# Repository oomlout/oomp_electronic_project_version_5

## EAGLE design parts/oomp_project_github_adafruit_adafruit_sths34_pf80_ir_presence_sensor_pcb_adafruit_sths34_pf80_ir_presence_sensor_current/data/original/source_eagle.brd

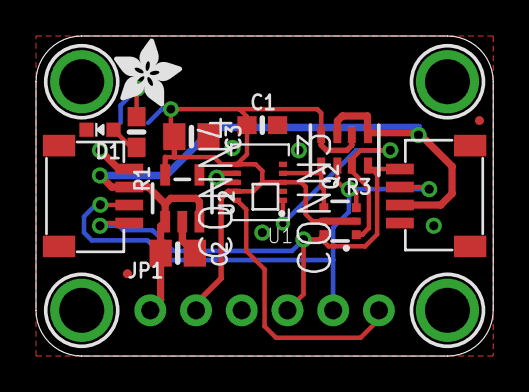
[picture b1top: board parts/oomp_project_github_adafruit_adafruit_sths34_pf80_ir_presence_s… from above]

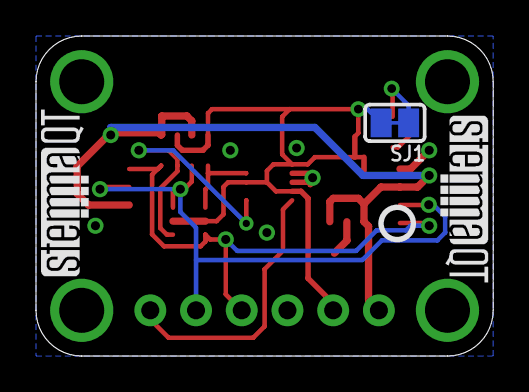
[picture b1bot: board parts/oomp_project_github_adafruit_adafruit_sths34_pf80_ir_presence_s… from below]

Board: 2 copper layers, 25.4 x 17.8 mm, 36 parts (8 on the bottom side), 10 nets.

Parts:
C1: 0.1uF; 0603-NO
C2, C3: 10uF; 0805-NO
CONN3, CONN4: STEMMA_I2C_QT; JST_SH4
D1: GREEN; CHIPLED_0603_NOOUTLINE
FID3, FID4: FIDUCIAL_0.5MM
JP1: 1X06_ROUND_70
PLABEL0: PLABEL0
PLABEL1: PLABEL1
PLABEL2: PLABEL2
PLABEL3: PLABEL3
PLABEL4: PLABEL4
PLABEL5: PLABEL5
PLABEL6: PLABEL6
PLABEL7: PLABEL7
PLABEL8: PLABEL8
PLABEL9: PLABEL9
PLABEL10: PLABEL10
PLABEL11: PLABEL11
PLABEL12: PLABEL12
Q2: BSS138; SOT363
R1: 10K; 0603-NO
R3: 10K Pack; RESPACK_4X0603
SJ1: SOLDERJUMPER_CLOSEDWIRE
U1: STHS34PF80TR; XDCR_STHS34PF80TR
U2: AP2127K-3.3; SOT23-5
U$1, U$17, U$19, U$21: MOUNTINGHOLE2.5; MOUNTINGHOLE_2.5_PLATED
U$22: ADAFRUIT_3.5MM
U$25: PCBFEAT-REV-040
U$30, U$31: STEMMAQT

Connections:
3.3V: C1.1, C3.1, JP1.2, Q2.2, Q2.5, R3.2, R3.4, SJ1.2, U1.3, U1.6, U1.9, U2.5
GND: C1.2, C2.2, C3.2, CONN3.1, CONN3.MT1, CONN3.MT2, CONN4.1, CONN4.MT1, CONN4.MT2, D1.C, JP1.3, U1.2, U1.7, U1.8, U2.2
INT: JP1.6, U1.10
unnamed: D1.A, R1.2
unnamed: R1.1, SJ1.1
SCL: CONN3.4, CONN4.4, JP1.4, Q2.6, R3.8
SCL_3V: Q2.1, R3.7, U1.1
SDA: CONN3.3, CONN4.3, JP1.5, Q2.3, R3.6
SDA_3V: Q2.4, R3.5, U1.4
VCC: C2.1, CONN3.2, CONN4.2, JP1.1, R3.1, R3.3, U2.1, U2.3

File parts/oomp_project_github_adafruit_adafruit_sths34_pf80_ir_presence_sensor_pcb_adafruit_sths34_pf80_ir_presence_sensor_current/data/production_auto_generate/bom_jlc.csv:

Comment,Designator,Footprint,LCSC Part #
,JP1,Adafruit STHS34PF80 IR Presence Sensor-import-fps:1X06_ROUND_70,C37208
,U$22,Adafruit STHS34PF80 IR Presence Sensor-import-fps:ADAFRUIT_3.5MM,
,U$25,Adafruit STHS34PF80 IR Presence Sensor-import-fps:PCBFEAT-REV-040,
,PLABEL0,Adafruit STHS34PF80 IR Presence Sensor-import-fps:PLABEL0,
,PLABEL1,Adafruit STHS34PF80 IR Presence Sensor-import-fps:PLABEL1,
,PLABEL10,Adafruit STHS34PF80 IR Presence Sensor-import-fps:PLABEL10,
,PLABEL11,Adafruit STHS34PF80 IR Presence Sensor-import-fps:PLABEL11,
,PLABEL12,Adafruit STHS34PF80 IR Presence Sensor-import-fps:PLABEL12,
,PLABEL2,Adafruit STHS34PF80 IR Presence Sensor-import-fps:PLABEL2,
,PLABEL3,Adafruit STHS34PF80 IR Presence Sensor-import-fps:PLABEL3,
,PLABEL4,Adafruit STHS34PF80 IR Presence Sensor-import-fps:PLABEL4,
,PLABEL5,Adafruit STHS34PF80 IR Presence Sensor-import-fps:PLABEL5,
,PLABEL6,Adafruit STHS34PF80 IR Presence Sensor-import-fps:PLABEL6,
,PLABEL7,Adafruit STHS34PF80 IR Presence Sensor-import-fps:PLABEL7,
,PLABEL8,Adafruit STHS34PF80 IR Presence Sensor-import-fps:PLABEL8,
,PLABEL9,Adafruit STHS34PF80 IR Presence Sensor-import-fps:PLABEL9,
,"U$30,U$31",Adafruit STHS34PF80 IR Presence Sensor-import-fps:STEMMAQT,
0.1uF,C1,Adafruit STHS34PF80 IR Presence Sensor-import-fps:0603-NO,C14663
10K,R1,Adafruit STHS34PF80 IR Presence Sensor-import-fps:0603-NO,C98220
10K Pack,R3,Adafruit STHS34PF80 IR Presence Sensor-import-fps:RESPACK_4X0603,C98220
10uF,"C2,C3",Adafruit STHS34PF80 IR Presence Sensor-import-fps:0805-NO,
AP2127K-3.3,U2,Adafruit STHS34PF80 IR Presence Sensor-import-fps:SOT23-5,
BSS138,Q2,Adafruit STHS34PF80 IR Presence Sensor-import-fps:SOT363,
GREEN,D1,Adafruit STHS34PF80 IR Presence Sensor-import-fps:CHIPLED_0603_NOOUTLINE,
STEMMA_I2C_QT,"CONN3,CONN4",Adafruit STHS34PF80 IR Presence Sensor-import-fps:JST_SH4,C160404
STHS34PF80TR,U1,Adafruit STHS34PF80 IR Presence Sensor-import-fps:XDCR_STHS34PF80TR,

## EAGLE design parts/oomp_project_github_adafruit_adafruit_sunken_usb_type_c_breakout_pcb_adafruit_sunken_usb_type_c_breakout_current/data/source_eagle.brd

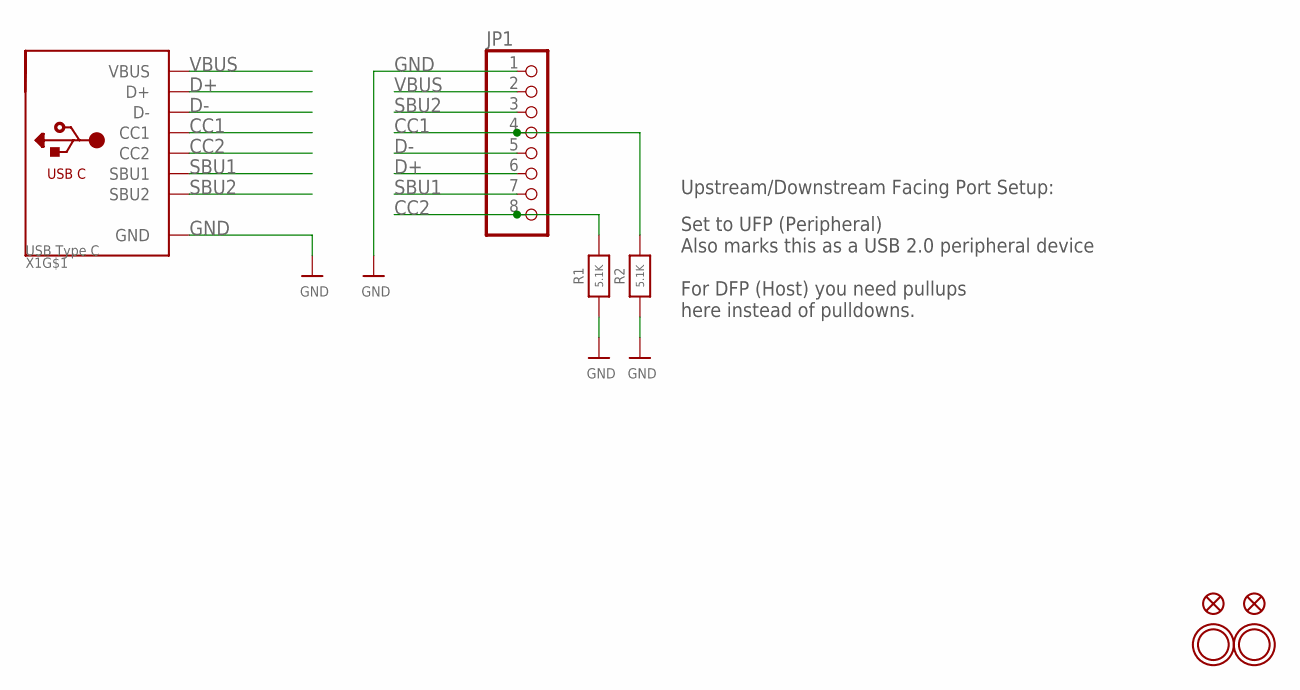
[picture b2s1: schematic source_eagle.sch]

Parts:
FID1, FID2: FIDUCIAL_0.5MM
JP1: HEADER-1X876MIL; 1X08_ROUND_76
R1, R2: 5.1K; 0603-NO
U$1, U$2: MOUNTINGHOLE2.5; MOUNTINGHOLE_2.5_PLATED
X1: USB Type C; USB_C_SINK

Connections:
CC1: JP1.4, R2.2, X1.A5 (CC1)
CC2: JP1.8, R1.2, X1.B5 (CC2)
D+: JP1.6, X1.A6 (D+), X1.B6 (D+)
D-: JP1.5, X1.A7 (D-), X1.B7 (D-)
GND: JP1.1, R1.1, R2.1, X1.A1B12 (GND), X1.B1A12 (GND)
SBU1: JP1.7, X1.A8 (SBU1)
SBU2: JP1.3, X1.B8 (SBU2)
VBUS: JP1.2, X1.A4B9 (VBUS), X1.B4A9 (VBUS)

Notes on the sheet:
Set to UFP (Peripheral) Also marks this as a USB 2.0 peripheral device For DFP (Host) you need pullups here instead of pulldowns.
Upstream/Downstream Facing Port Setup:

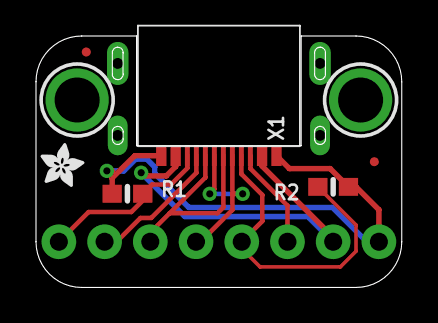
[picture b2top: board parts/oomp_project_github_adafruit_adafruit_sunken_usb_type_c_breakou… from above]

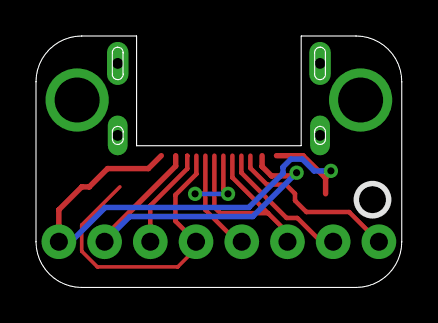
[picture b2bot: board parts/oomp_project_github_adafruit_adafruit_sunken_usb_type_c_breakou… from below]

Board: 2 copper layers, 20.3 x 14.0 mm, 21 parts (3 on the bottom side), 8 nets.

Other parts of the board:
PLABEL0: PLABEL0
PLABEL1: PLABEL1
PLABEL2: PLABEL2
PLABEL3: PLABEL3
PLABEL4: PLABEL4
PLABEL5: PLABEL5
PLABEL6: PLABEL6
PLABEL7: PLABEL7
PLABEL8: PLABEL8
PLABEL9: PLABEL9
PLABEL10: PLABEL10
U$3: ADAFRUIT_2.5MM
U$8: PCBFEAT-REV-040

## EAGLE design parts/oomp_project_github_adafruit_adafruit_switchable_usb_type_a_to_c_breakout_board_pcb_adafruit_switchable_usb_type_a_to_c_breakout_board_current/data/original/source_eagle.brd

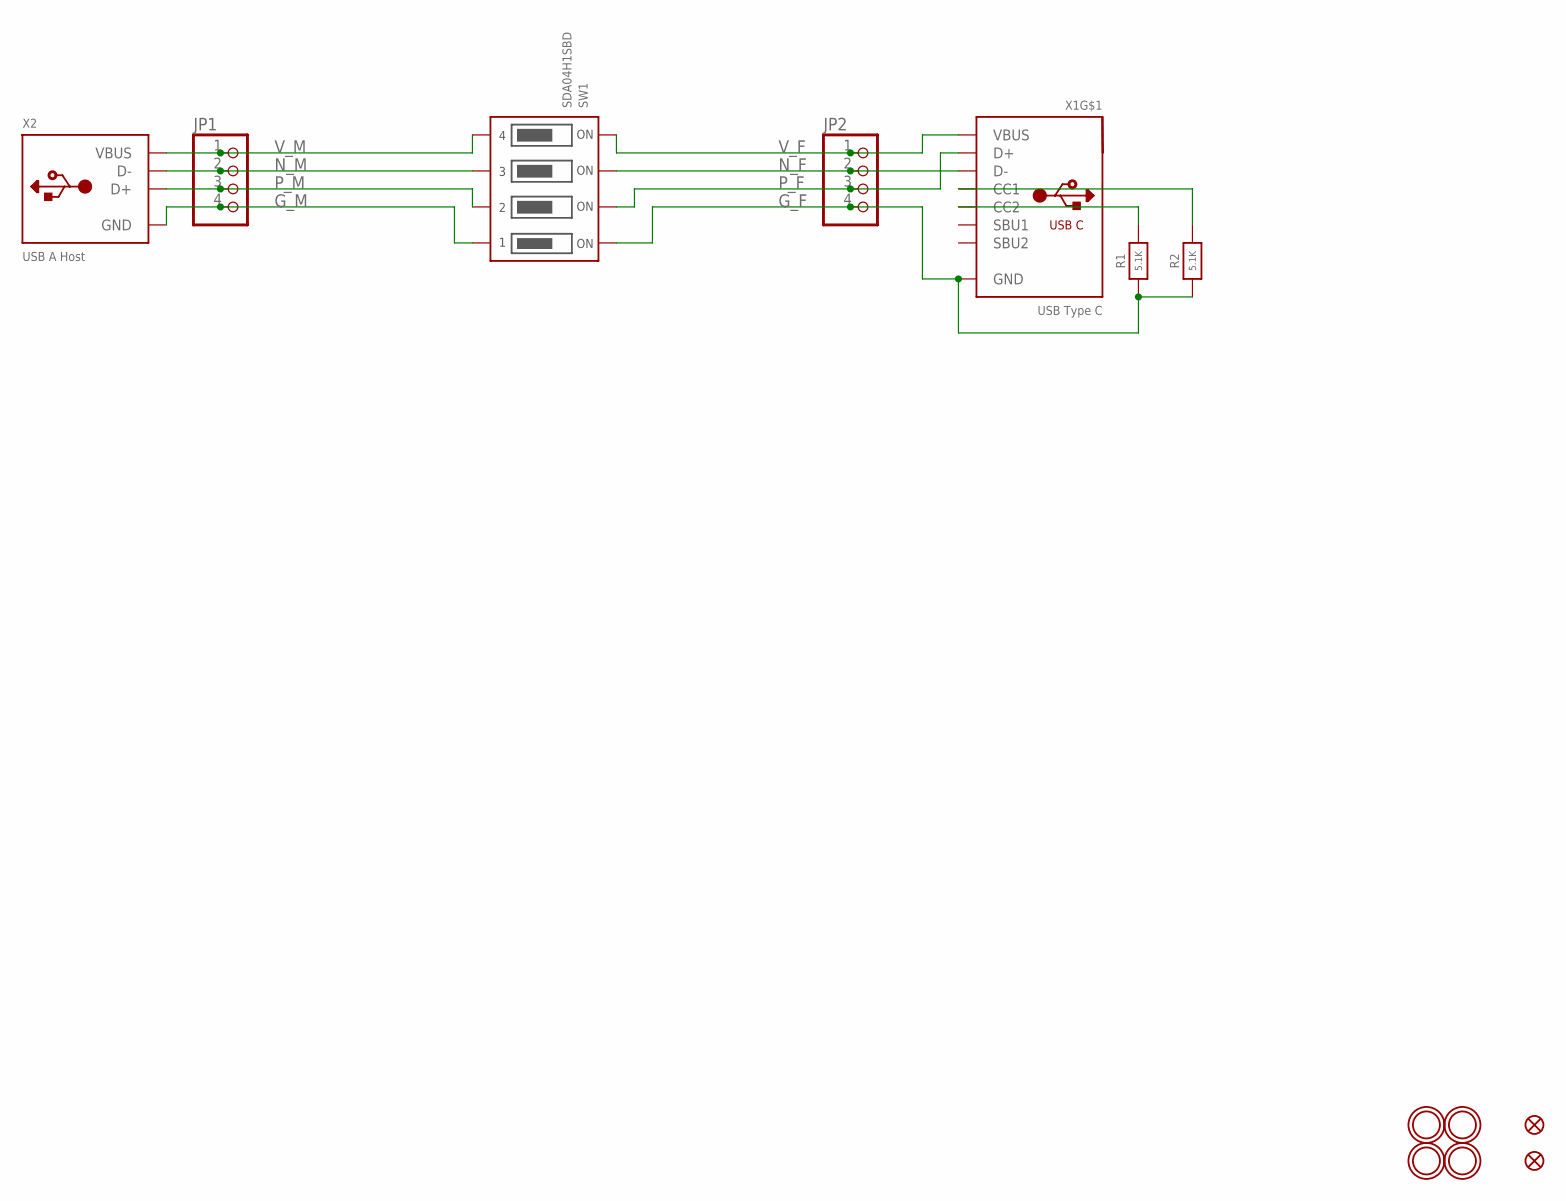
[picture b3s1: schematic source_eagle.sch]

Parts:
FID1, FID2: FIDUCIAL_1MM
JP1, JP2: HEADER-1X4ROUND; 1X04_ROUND
R1, R2: 5.1K; 0603-NO
SW1: SDA04H1SBD; DIPSWITCH_4PIN
U$1, U$2, U$3, U$4: MOUNTINGHOLE2.5; MOUNTINGHOLE_2.5_PLATED
X1: USB Type C; USB_C_CUSB31-CFM2AX-01-X
X2: USB A Host; USB_HOST-PTH

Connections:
G_F: JP2.4, R1.1, R2.1, SW1.1ON, X1.A1B12 (GND), X1.B1A12 (GND)
G_M: JP1.4, SW1.1OFF, X2.GND
unnamed: R1.2, X1.B5 (CC2)
unnamed: R2.2, X1.A5 (CC1)
N_F: JP2.2, SW1.3ON, X1.A7 (D-), X1.B7 (D-)
N_M: JP1.2, SW1.3OFF, X2.D-
P_F: JP2.3, SW1.2ON, X1.A6 (D+), X1.B6 (D+)
P_M: JP1.3, SW1.2OFF, X2.D+
V_F: JP2.1, SW1.4ON, X1.A4B9 (VBUS), X1.B4A9 (VBUS)
V_M: JP1.1, SW1.4OFF, X2.VBUS

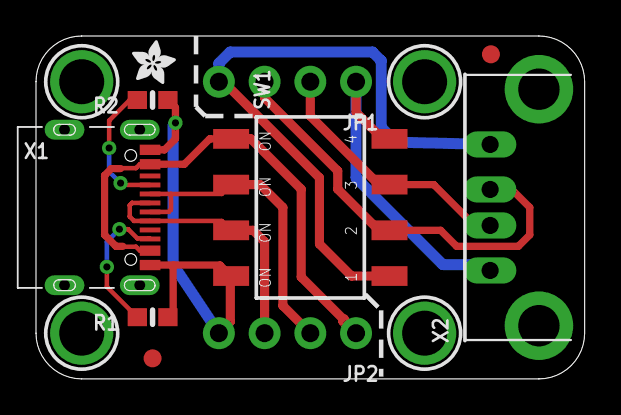
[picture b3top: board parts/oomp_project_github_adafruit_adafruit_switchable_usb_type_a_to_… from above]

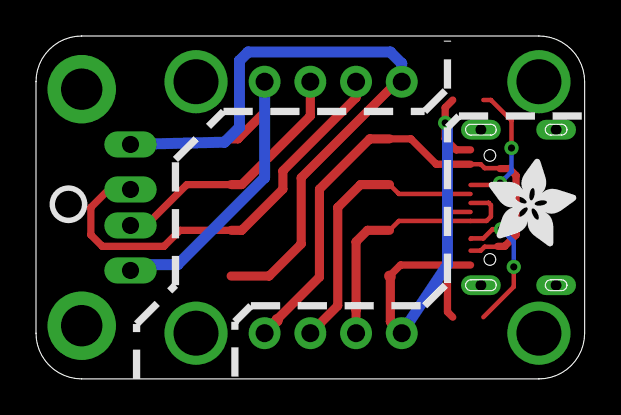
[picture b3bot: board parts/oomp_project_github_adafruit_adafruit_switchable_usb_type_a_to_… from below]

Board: 2 copper layers, 30.5 x 19.1 mm, 41 parts (11 on the bottom side), 10 nets.

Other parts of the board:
PLABEL0: PLABEL0
PLABEL1: PLABEL1
PLABEL2: PLABEL2
PLABEL3: PLABEL3
PLABEL4: PLABEL4
PLABEL5: PLABEL5
PLABEL6: PLABEL6
PLABEL7: PLABEL7
PLABEL8: PLABEL8
PLABEL9: PLABEL9
PLABEL10: PLABEL10
PLABEL11: PLABEL11
PLABEL12: PLABEL12
PLABEL13: PLABEL13
PLABEL14: PLABEL14
PLABEL15: PLABEL15
PLABEL16: PLABEL16
PLABEL17: PLABEL17
PLABEL18: PLABEL18
PLABEL19: PLABEL19
PLABEL20: PLABEL20
PLABEL21: PLABEL21
PLABEL22: PLABEL22
PLABEL23: PLABEL23
PLABEL24: PLABEL24
U$5: ADAFRUIT_2.5MM
U$6: ADAFRUIT_5MM
U$8: PCBFEAT-REV-040

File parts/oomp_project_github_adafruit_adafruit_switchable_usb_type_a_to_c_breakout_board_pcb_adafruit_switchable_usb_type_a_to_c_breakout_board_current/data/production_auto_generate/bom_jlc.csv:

Comment,Designator,Footprint,LCSC Part #
,"JP1,JP2",1X04_ROUND,C42431795
,U$5,ADAFRUIT_2.5MM,
,U$6,ADAFRUIT_5MM,
,U$8,PCBFEAT-REV-040,
,PLABEL0,PLABEL0,
,PLABEL1,PLABEL1,
,PLABEL10,PLABEL10,
,PLABEL11,PLABEL11,
,PLABEL12,PLABEL12,
,PLABEL13,PLABEL13,
,PLABEL14,PLABEL14,
,PLABEL15,PLABEL15,
,PLABEL16,PLABEL16,
,PLABEL17,PLABEL17,
,PLABEL18,PLABEL18,
,PLABEL19,PLABEL19,
,PLABEL2,PLABEL2,
,PLABEL20,PLABEL20,
,PLABEL21,PLABEL21,
,PLABEL22,PLABEL22,
,PLABEL23,PLABEL23,
,PLABEL24,PLABEL24,
,PLABEL3,PLABEL3,
,PLABEL4,PLABEL4,
,PLABEL5,PLABEL5,
,PLABEL6,PLABEL6,
,PLABEL7,PLABEL7,
,PLABEL8,PLABEL8,
,PLABEL9,PLABEL9,
5.1K,"R1,R2",0603-NO,C23186
SDA04H1SBD,SW1,DIPSWITCH_4PIN,
USB A Host,X2,USB_HOST-PTH,
USB Type C,X1,USB_C_CUSB31-CFM2AX-01-X,

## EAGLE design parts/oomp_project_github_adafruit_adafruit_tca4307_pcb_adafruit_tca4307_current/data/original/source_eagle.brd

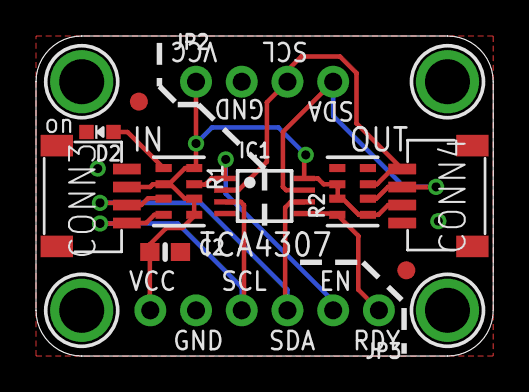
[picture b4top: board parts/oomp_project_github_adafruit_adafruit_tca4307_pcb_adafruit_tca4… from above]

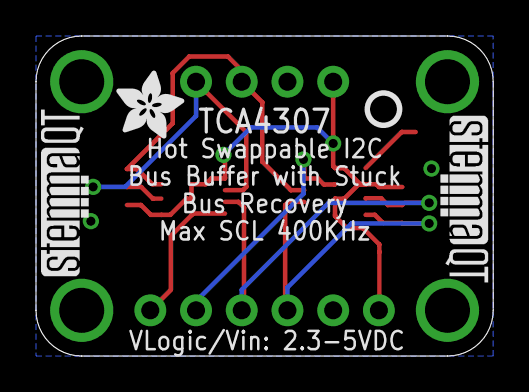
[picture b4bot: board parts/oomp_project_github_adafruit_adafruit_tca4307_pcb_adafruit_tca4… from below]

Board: 2 copper layers, 25.4 x 17.8 mm, 19 parts (4 on the bottom side), 9 nets.

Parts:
C2: 0.1uF; 0603-NO
CONN3, CONN4: STEMMA_I2C_QT; JST_SH4
D2: GREEN; CHIPLED_0603_NOOUTLINE
FID3, FID4: FIDUCIAL_1MM
IC1: TCA4307; TSSOP8
JP2: 1X04_ROUND
JP3: 1X06_ROUND_70
R1, R2: 10K; RESPACK_4X0603
U$1, U$17, U$19, U$21: MOUNTINGHOLE2.5; MOUNTINGHOLE_2.5_PLATED
U$2: ADAFRUIT_3.5MM
U$25: PCBFEAT-REV-040
U$30, U$31: STEMMAQT

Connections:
EN: IC1.1, JP3.2, R1.7
GND: C2.2, CONN3.1, CONN4.1, D2.C, IC1.4, JP2.2, JP3.5
unnamed: D2.A, R1.1
READY: IC1.5, JP3.1, R2.8
SCL_IN: CONN3.4, IC1.3, JP3.4, R1.4
SCL_OUT: CONN4.4, IC1.2, JP2.3, R2.3
SDA_IN: CONN3.3, IC1.6, JP3.3, R1.3
SDA_OUT: CONN4.3, IC1.7, JP2.4, R2.2
VCC: C2.1, CONN3.2, CONN4.2, IC1.8, JP2.1, JP3.6, R1.2, R1.5, R1.6, R1.8, R2.1, R2.6, R2.7

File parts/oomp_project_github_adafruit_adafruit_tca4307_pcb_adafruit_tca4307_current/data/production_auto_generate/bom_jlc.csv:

Comment,Designator,Footprint,LCSC Part #
,JP2,Adafruit TCA4307-import-fps:1X04_ROUND,C42431795
,JP3,Adafruit TCA4307-import-fps:1X06_ROUND_70,C37208
,U$2,Adafruit TCA4307-import-fps:ADAFRUIT_3.5MM,
,U$25,Adafruit TCA4307-import-fps:PCBFEAT-REV-040,
,"U$30,U$31",Adafruit TCA4307-import-fps:STEMMAQT,
0.1uF,C2,Adafruit TCA4307-import-fps:0603-NO,C14663
10K,"R1,R2",Adafruit TCA4307-import-fps:RESPACK_4X0603,C98220
GREEN,D2,Adafruit TCA4307-import-fps:CHIPLED_0603_NOOUTLINE,
STEMMA_I2C_QT,"CONN3,CONN4",Adafruit TCA4307-import-fps:JST_SH4,C160404
TCA4307,IC1,Adafruit TCA4307-import-fps:TSSOP8,

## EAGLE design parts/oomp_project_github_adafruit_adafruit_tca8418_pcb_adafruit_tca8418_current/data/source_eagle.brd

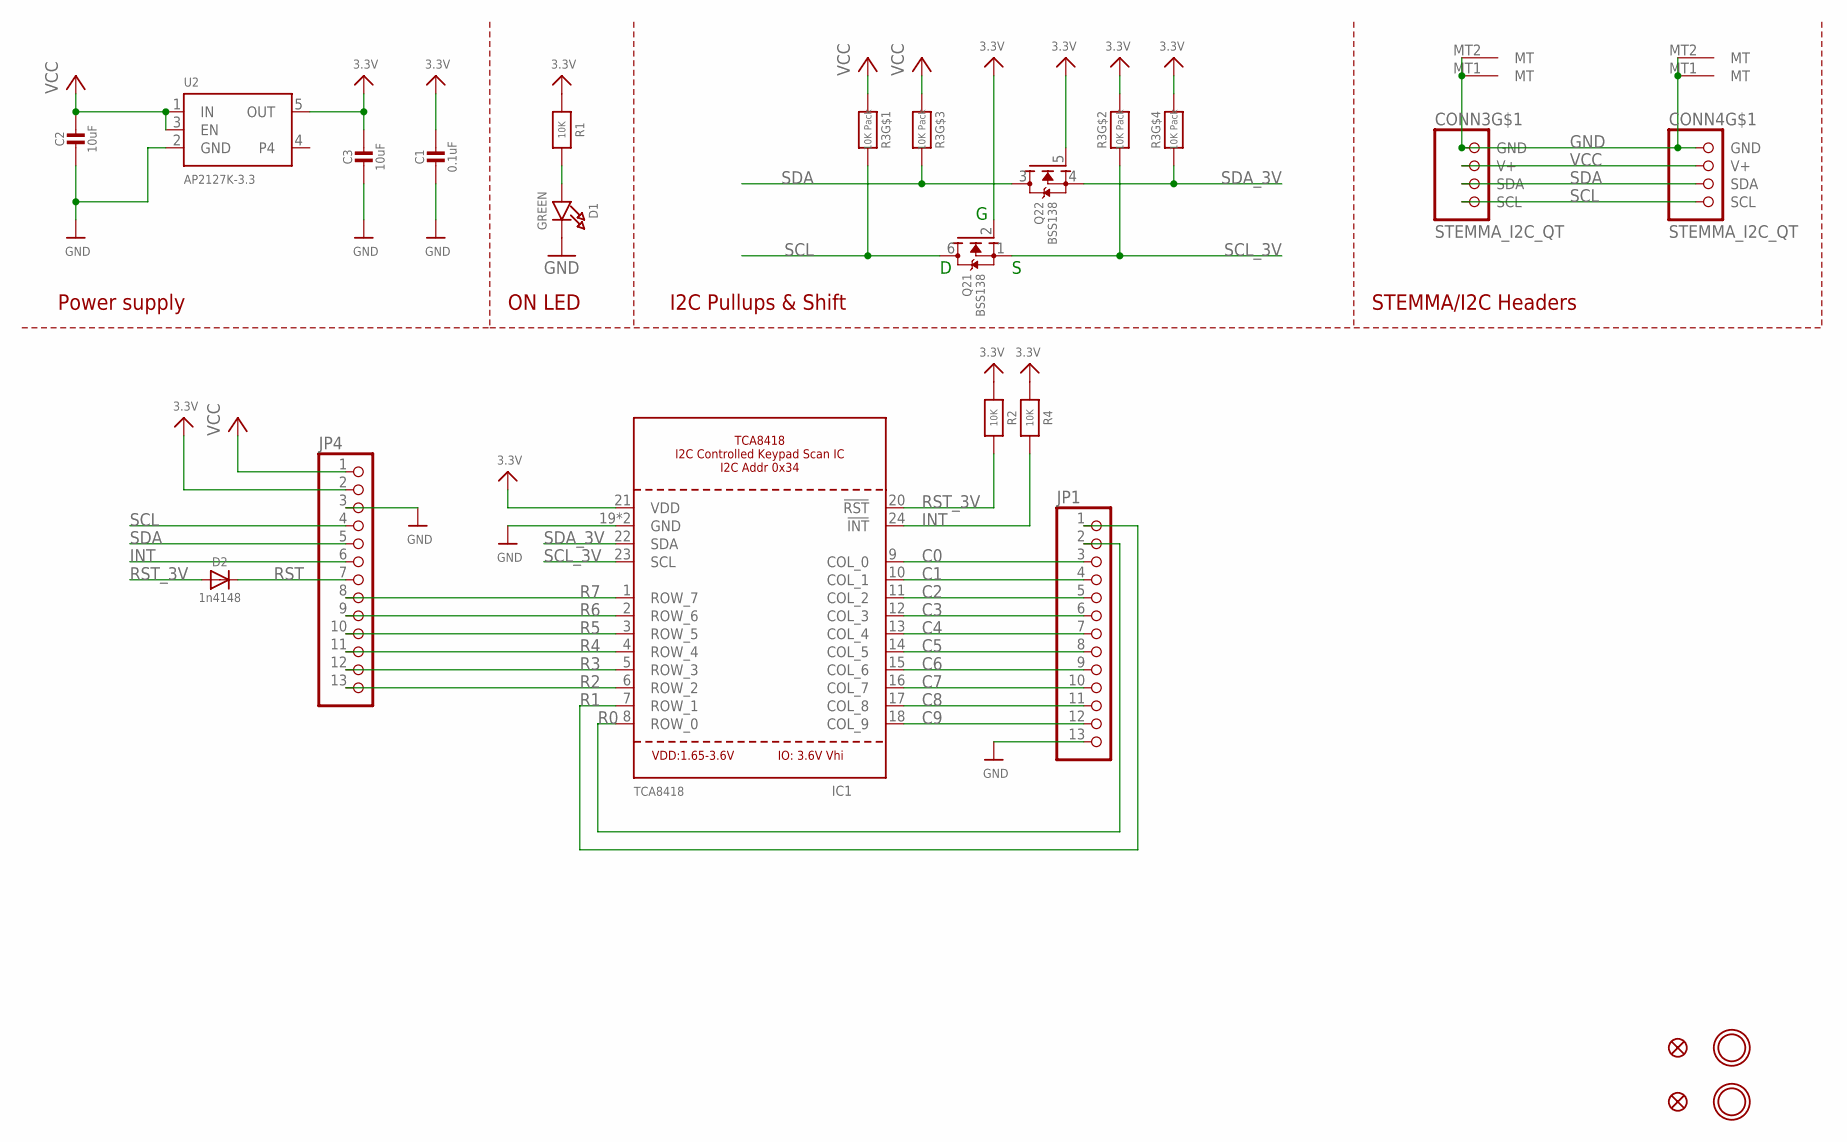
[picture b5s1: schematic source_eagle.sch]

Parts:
C1: 0.1uF; 0603-NO
C2, C3: 10uF; 0805-NO
CONN3, CONN4: STEMMA_I2C_QT; JST_SH4
D1: GREEN; CHIPLED_0603_NOOUTLINE
D2: 1n4148; SOD-323
FID3, FID4: FIDUCIAL_1MM
IC1: TCA8418; QFN24_4MM_SMSC
JP1, JP4: HEADER-1X13; 1X13_ROUND_70
Q2: BSS138; SOT363
R1, R2, R4: 10K; 0603-NO
R3: 10K Pack; RESPACK_4X0603
U2: AP2127K-3.3; SOT23-5
U$1, U$17: MOUNTINGHOLE2.5; MOUNTINGHOLE_2.5_PLATED

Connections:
3.3V: C1.1, C3.1, IC1.21 (VDD), JP4.2, Q2.2 (G), Q2.5 (G), R1.1, R2.1, R3.2 (1), R3.4 (1), R4.1, U2.5 (OUT)
C0: IC1.9 (COL_0), JP1.3
C1: IC1.10 (COL_1), JP1.4
C2: IC1.11 (COL_2), JP1.5
C3: IC1.12 (COL_3), JP1.6
C4: IC1.13 (COL_4), JP1.7
C5: IC1.14 (COL_5), JP1.8
C6: IC1.15 (COL_6), JP1.9
C7: IC1.16 (COL_7), JP1.10
C8: IC1.17 (COL_8), JP1.11
C9: IC1.18 (COL_9), JP1.12
GND: C1.2, C2.2, C3.2, CONN3.1 (GND), CONN3.MT1 (MT), CONN3.MT2 (MT), CONN4.1 (GND), CONN4.MT1 (MT), CONN4.MT2 (MT), D1.C, IC1.19 (GND), IC1.THERM (GND), JP1.13, JP4.3, U2.2 (GND)
INT: IC1.24 (!INT), JP4.6, R4.2
unnamed: D1.A, R1.2
R0: IC1.8 (ROW_0), JP1.2
R1: IC1.7 (ROW_1), JP1.1
R2: IC1.6 (ROW_2), JP4.13
R3: IC1.5 (ROW_3), JP4.12
R4: IC1.4 (ROW_4), JP4.11
R5: IC1.3 (ROW_5), JP4.10
R6: IC1.2 (ROW_6), JP4.9
R7: IC1.1 (ROW_7), JP4.8
RST: D2.C, JP4.7
RST_3V: D2.A, IC1.20 (!RST), R2.2
SCL: CONN3.4 (SCL), CONN4.4 (SCL), JP4.4, Q2.6 (D), R3.8 (2)
SCL_3V: IC1.23 (SCL), Q2.1 (S), R3.7 (2)
SDA: CONN3.3 (SDA), CONN4.3 (SDA), JP4.5, Q2.3 (D), R3.6 (2)
SDA_3V: IC1.22 (SDA), Q2.4 (S), R3.5 (2)
VCC: C2.1, CONN3.2 (V+), CONN4.2 (V+), JP4.1, R3.1, R3.3 (1), U2.1 (IN), U2.3 (EN)

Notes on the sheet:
I2C Pullups & Shift
STEMMA/I2C Headers
ON LED
Power supply

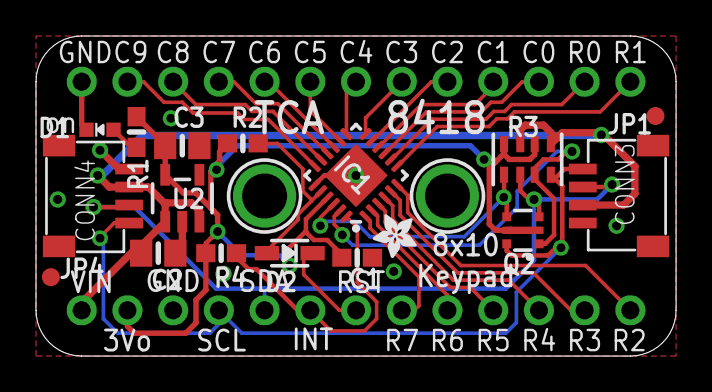
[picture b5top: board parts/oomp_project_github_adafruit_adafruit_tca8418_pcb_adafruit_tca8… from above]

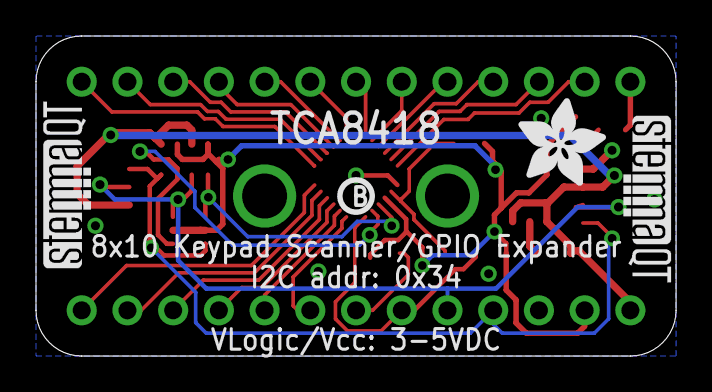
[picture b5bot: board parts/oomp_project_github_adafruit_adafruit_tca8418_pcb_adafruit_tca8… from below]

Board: 2 copper layers, 35.6 x 17.8 mm, 25 parts (4 on the bottom side), 29 nets.

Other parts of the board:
U$12: PCBFEAT-REV-040
U$19: ADAFRUIT_5MM
U$20: ADAFRUIT_2.5MM
U$30, U$31: STEMMAQT

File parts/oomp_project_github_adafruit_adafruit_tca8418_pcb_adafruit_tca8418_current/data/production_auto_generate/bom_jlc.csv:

Comment,Designator,Footprint,LCSC Part #
,"JP1,JP4",Adafruit TCA8418-import-fps:1X13_ROUND_70,C2894936
,U$20,Adafruit TCA8418-import-fps:ADAFRUIT_2.5MM,
,U$19,Adafruit TCA8418-import-fps:ADAFRUIT_5MM,
,U$12,Adafruit TCA8418-import-fps:PCBFEAT-REV-040,
,"U$30,U$31",Adafruit TCA8418-import-fps:STEMMAQT,
0.1uF,C1,Adafruit TCA8418-import-fps:0603-NO,C14663
10K,"R1,R2,R4",Adafruit TCA8418-import-fps:0603-NO,C98220
10K Pack,R3,Adafruit TCA8418-import-fps:RESPACK_4X0603,C98220
10uF,"C2,C3",Adafruit TCA8418-import-fps:0805-NO,
1n4148,D2,Adafruit TCA8418-import-fps:SOD-323,
AP2127K-3.3,U2,Adafruit TCA8418-import-fps:SOT23-5,
BSS138,Q2,Adafruit TCA8418-import-fps:SOT363,
GREEN,D1,Adafruit TCA8418-import-fps:CHIPLED_0603_NOOUTLINE,
STEMMA_I2C_QT,"CONN3,CONN4",Adafruit TCA8418-import-fps:JST_SH4,C160404
TCA8418,IC1,Adafruit TCA8418-import-fps:QFN24_4MM_SMSC,

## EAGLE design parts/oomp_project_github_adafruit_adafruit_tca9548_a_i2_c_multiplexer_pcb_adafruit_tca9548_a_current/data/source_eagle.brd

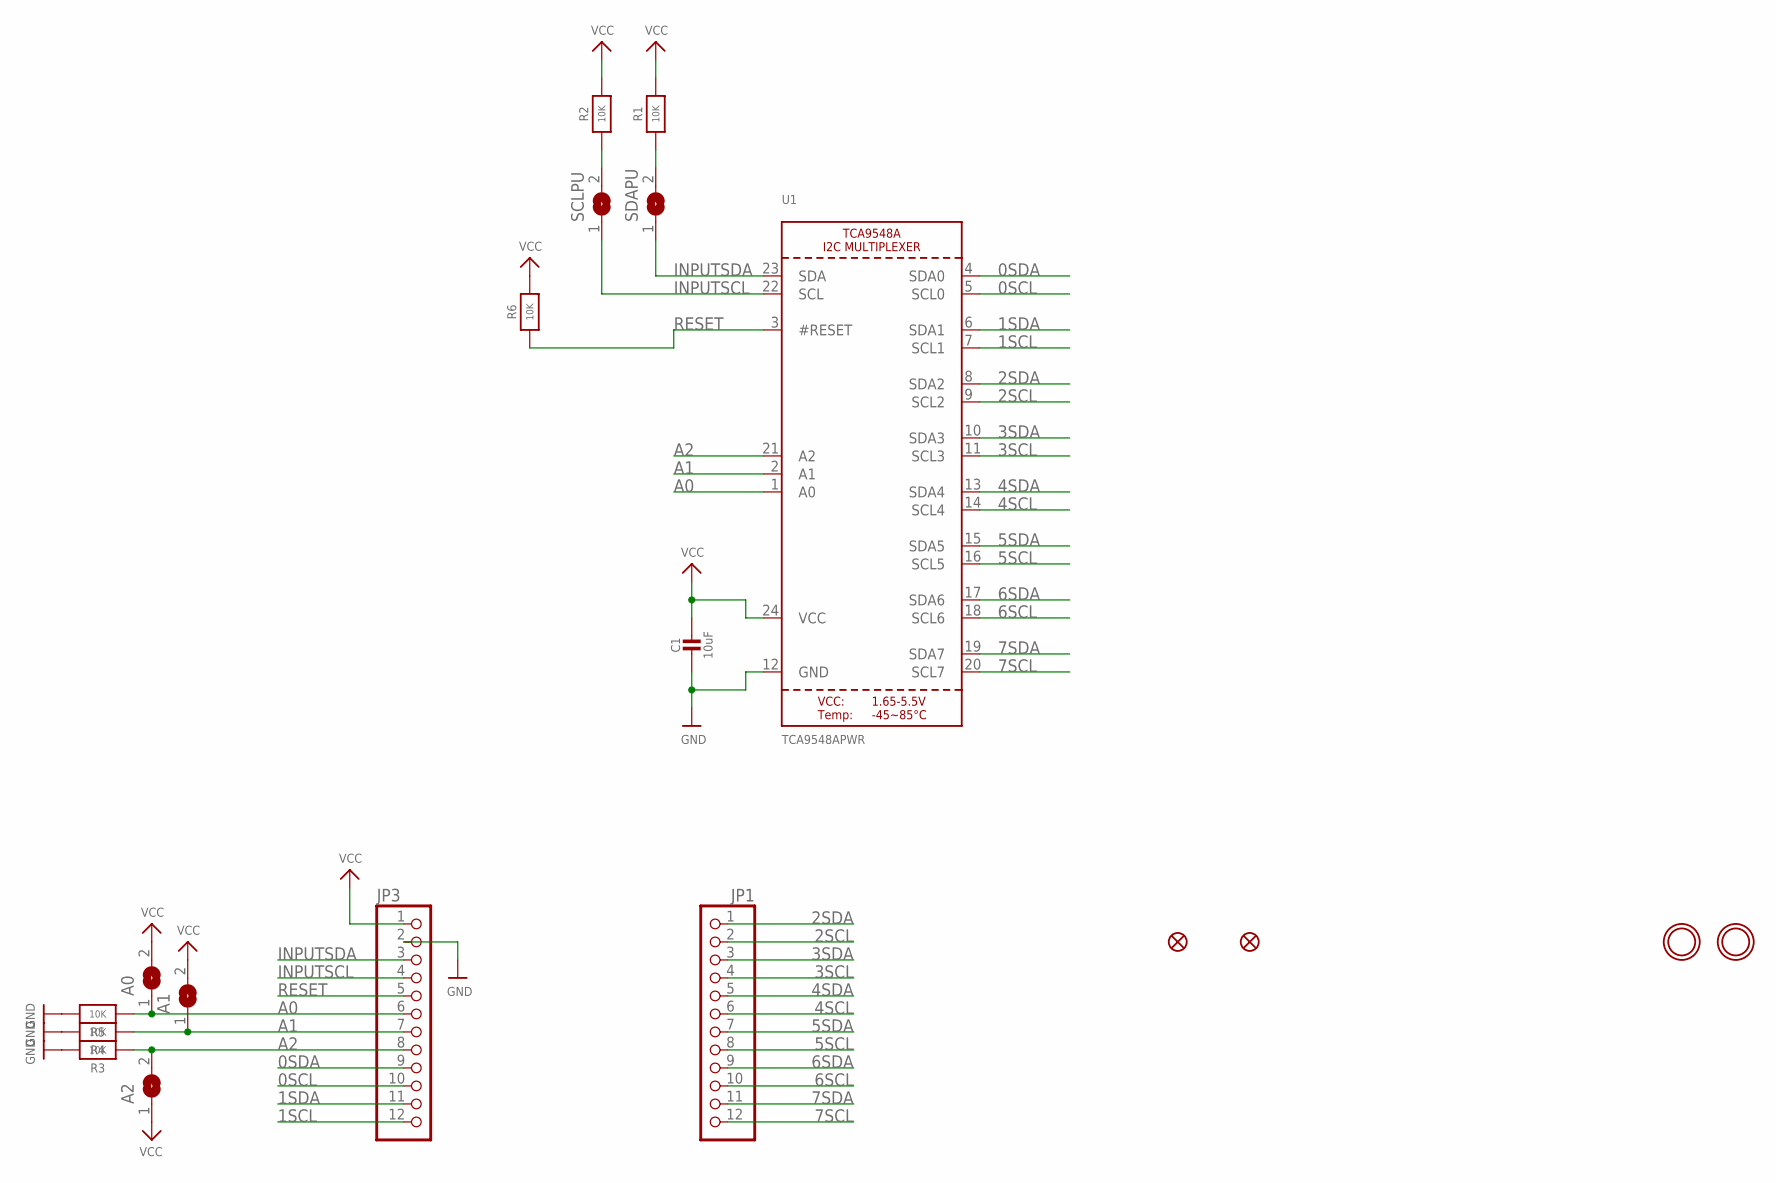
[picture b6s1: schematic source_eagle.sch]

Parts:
A0, A1, A2: SOLDERJUMPER; SOLDERJUMPER_ARROW_NOPASTE
C1: 10uF; 0805-NO
FID1, FID3: FIDUCIAL""; FIDUCIAL_1MM
JP1, JP3: HEADER-1X12; 1X12_ROUND
R1, R2, R3, R4, R5: 10K; 0805-NO
R6: 10K; _0805MP
SCLPU: SOLDERJUMPERCLOSED; SOLDERJUMPER_CLOSEDWIRE
SDAPU: SOLDERJUMPERCLOSED; SOLDERJUMPER_CLOSEDWIRE
U1: TCA9548APWR; TSSOP24
U$4, U$5: MOUNTINGHOLE2.5; MOUNTINGHOLE_2.5_PLATED

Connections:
0SCL: JP3.10, U1.5 (SCL0)
0SDA: JP3.9, U1.4 (SDA0)
1SCL: JP3.12, U1.7 (SCL1)
1SDA: JP3.11, U1.6 (SDA1)
2SCL: JP1.2, U1.9 (SCL2)
2SDA: JP1.1, U1.8 (SDA2)
3SCL: JP1.4, U1.11 (SCL3)
3SDA: JP1.3, U1.10 (SDA3)
4SCL: JP1.6, U1.14 (SCL4)
4SDA: JP1.5, U1.13 (SDA4)
5SCL: JP1.8, U1.16 (SCL5)
5SDA: JP1.7, U1.15 (SDA5)
6SCL: JP1.10, U1.18 (SCL6)
6SDA: JP1.9, U1.17 (SDA6)
7SCL: JP1.12, U1.20 (SCL7)
7SDA: JP1.11, U1.19 (SDA7)
A0: A0.1, JP3.6, R5.1, U1.1 (A0)
A1: A1.1, JP3.7, R4.1, U1.2 (A1)
A2: A2.2, JP3.8, R3.1, U1.21 (A2)
GND: C1.2, JP3.2, R3.2, R4.2, R5.2, U1.12 (GND)
INPUTSCL: JP3.4, SCLPU.1, U1.22 (SCL)
INPUTSDA: JP3.3, SDAPU.1, U1.23 (SDA)
unnamed: R2.1, SCLPU.2
unnamed: R1.1, SDAPU.2
RESET: JP3.5, R6.1, U1.3 (#RESET)
VCC: A0.2, A1.2, A2.1, C1.1, JP3.1, R1.2, R2.2, R6.2, U1.24 (VCC)

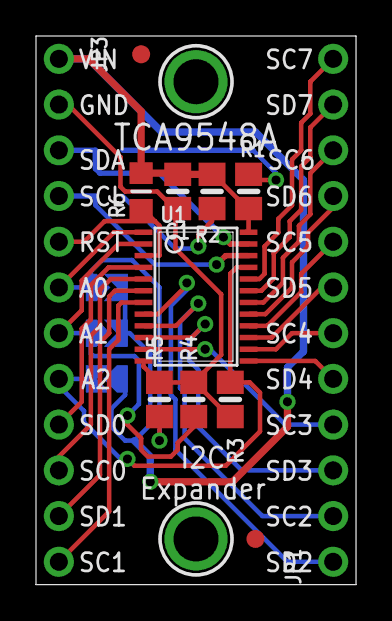
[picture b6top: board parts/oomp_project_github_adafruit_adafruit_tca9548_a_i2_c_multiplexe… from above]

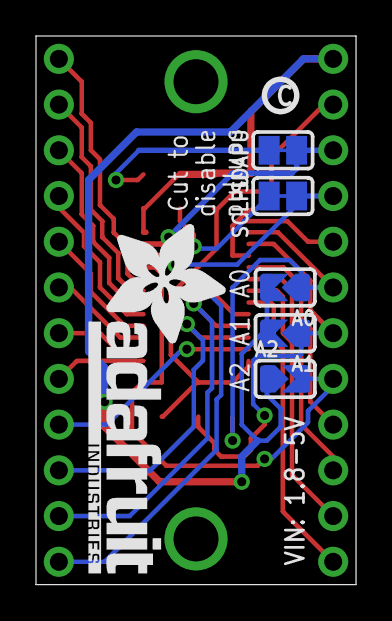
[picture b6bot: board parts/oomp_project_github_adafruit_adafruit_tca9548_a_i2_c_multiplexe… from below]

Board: 2 copper layers, 17.8 x 30.5 mm, 21 parts (7 on the bottom side), 26 nets.

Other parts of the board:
U$6: PCBFEAT-REV-040
U$7: ADAFRUIT_TEXT_20MM

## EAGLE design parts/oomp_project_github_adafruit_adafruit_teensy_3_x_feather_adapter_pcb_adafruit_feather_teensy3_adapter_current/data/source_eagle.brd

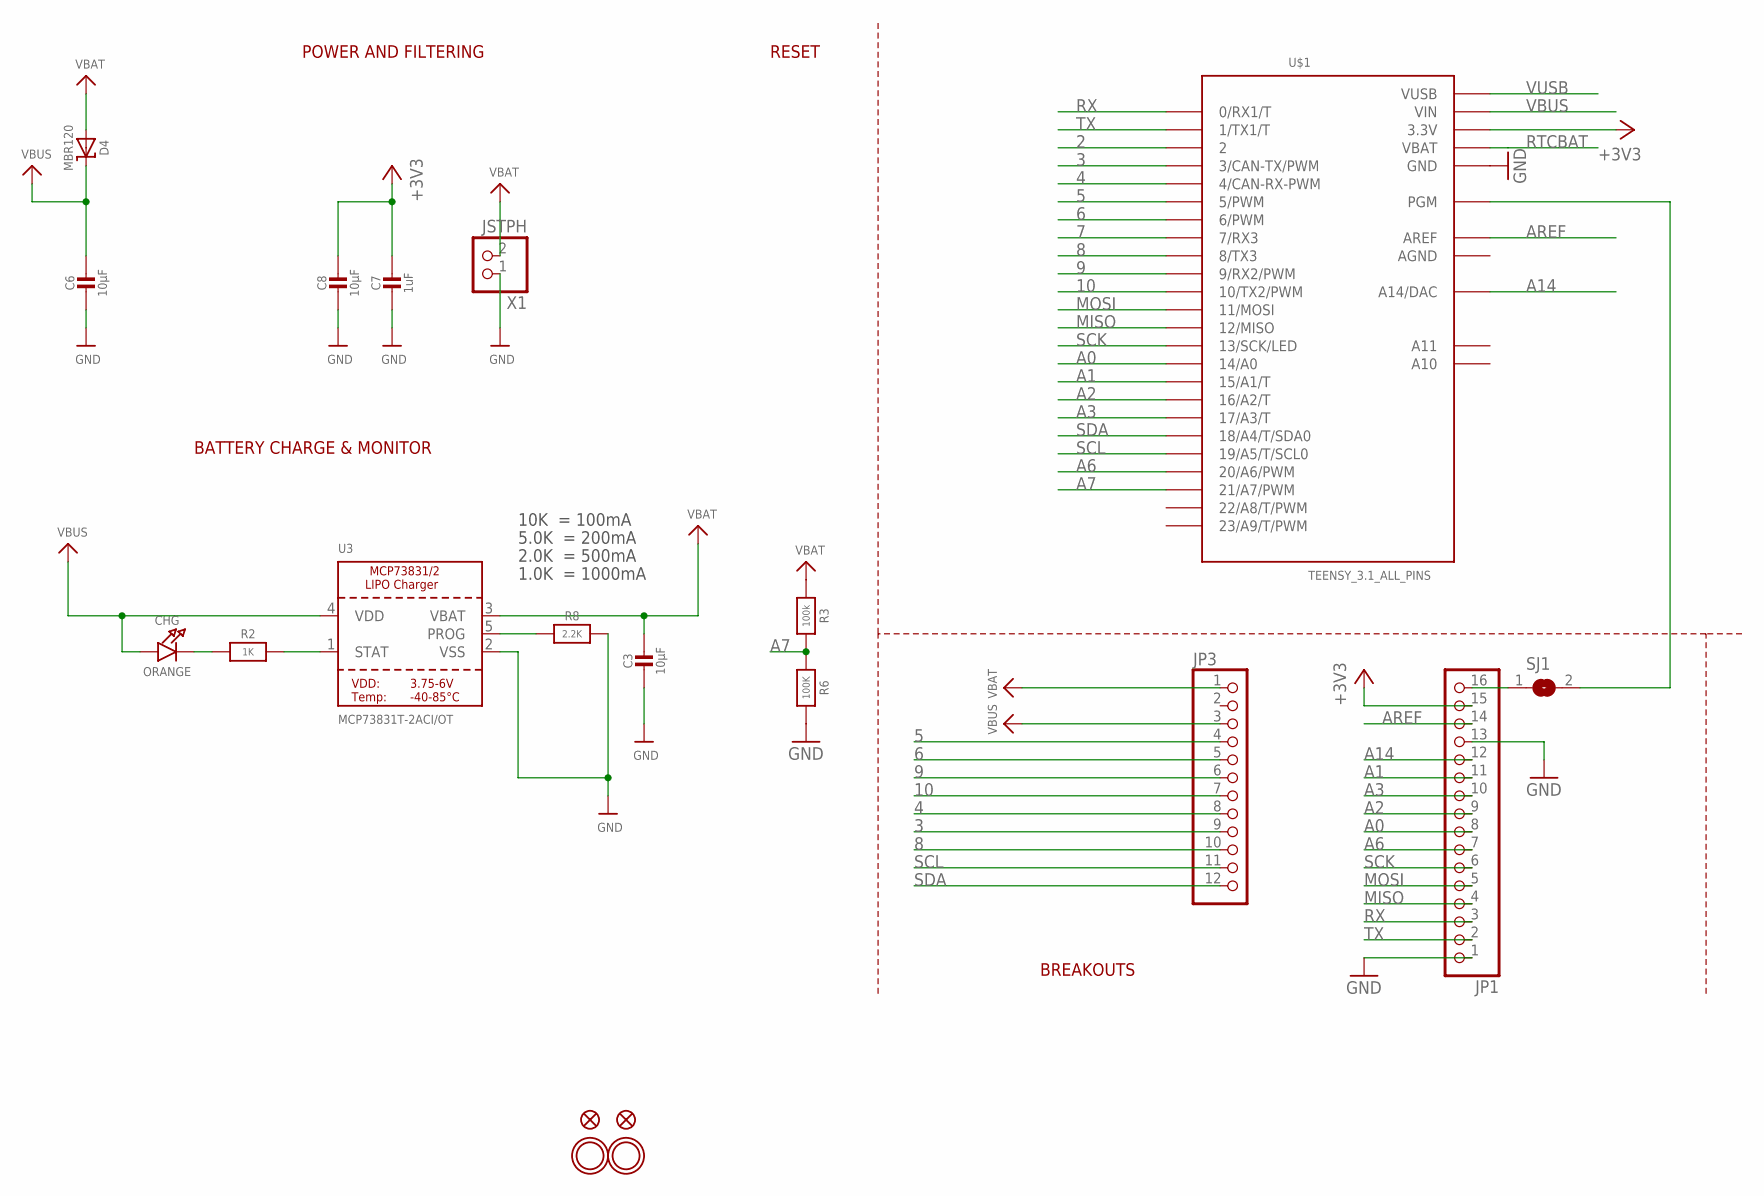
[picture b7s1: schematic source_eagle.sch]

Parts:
C3, C6, C8: 10µF; 0805-NO
C7: 1uF; 0603-NO
CHG: ORANGE; CHIPLED_0805_NOOUTLINE
D4: MBR120; SOD-123
JP1: HEADER-1X16ROUND; 1X16_ROUND
JP3: HEADER-1X12; 1X12_ROUND
R2: 1K; 0603-NO
R3: 100k; 0603-NO
R6: 100K; 0603-NO
R8: 2.2K; 0603-NO
SJ1: SOLDERJUMPERCLOSED; SOLDERJUMPER_CLOSEDWIRE
U3: MCP73831T-2ACI/OT; SOT23-5
U$1: TEENSY_3.1_ALL_PINS; TEENSY3-ALL_PINS
U$31, U$32: MOUNTINGHOLE2.5; MOUNTINGHOLE_2.5_PLATED
U$34, U$35: FIDUCIAL""; FIDUCIAL_1MM
X1: JSTPH; JSTPH2

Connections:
2: U$1.2
3: JP3.9, U$1.3 (3/CAN-TX/PWM)
4: JP3.8, U$1.4 (4/CAN-RX-PWM)
5: JP3.4, U$1.5 (5/PWM)
6: JP3.5, U$1.6 (6/PWM)
7: U$1.7 (7/RX3)
8: JP3.10, U$1.8 (8/TX3)
9: JP3.6, U$1.9 (9/RX2/PWM)
10: JP3.7, U$1.10 (10/TX2/PWM)
+3V3: C7.1, C8.1, JP1.15, U$1.3.3V, U$1.3.3V1 (3.3V)
A0: JP1.8, U$1.14/A0
A1: JP1.11, U$1.15/A1 (15/A1/T)
A2: JP1.9, U$1.16/A2 (16/A2/T)
A3: JP1.10, U$1.17/A3 (17/A3/T)
A6: JP1.7, U$1.20/A6 (20/A6/PWM)
A7: R3.2, R6.1, U$1.21/A7 (21/A7/PWM)
A14: JP1.12, U$1.RESET/DAC (A14/DAC)
AGND: U$1.AGND
AREF: JP1.14, U$1.AREF
BOOT: SJ1.2, U$1.PGM
GND: C3.2, C6.2, C7.2, C8.2, JP1.1, JP1.13, R6.2, R8.2, U3.2 (VSS), U$1.GND, U$1.GND1 (GND), X1.1
MISO: JP1.4, U$1.12 (12/MISO)
MOSI: JP1.5, U$1.11 (11/MOSI)
unnamed: CHG.C, R2.1
unnamed: R2.2, U3.1 (STAT)
unnamed: R8.1, U3.5 (PROG)
RST/BOOT: JP1.16, SJ1.1
RTCBAT: U$1.VBAT
RX: JP1.3, U$1.0 (0/RX1/T)
SCK: JP1.6, U$1.13 (13/SCK/LED)
SCL: JP3.11, U$1.19/A5 (19/A5/T/SCL0)
SDA: JP3.12, U$1.18/A4 (18/A4/T/SDA0)
TX: JP1.2, U$1.1 (1/TX1/T)
VBAT: C3.1, D4.A, JP3.1, R3.1, U3.3 (VBAT), X1.2
VBUS: C6.1, CHG.A, D4.C, JP3.3, U3.4 (VDD), U$1.VIN
VUSB: U$1.VUSB

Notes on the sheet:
POWER AND FILTERING
RESET
10K = 100mA
5.0K = 200mA
2.0K = 500mA
1.0K = 1000mA
BATTERY CHARGE & MONITOR
BREAKOUTS

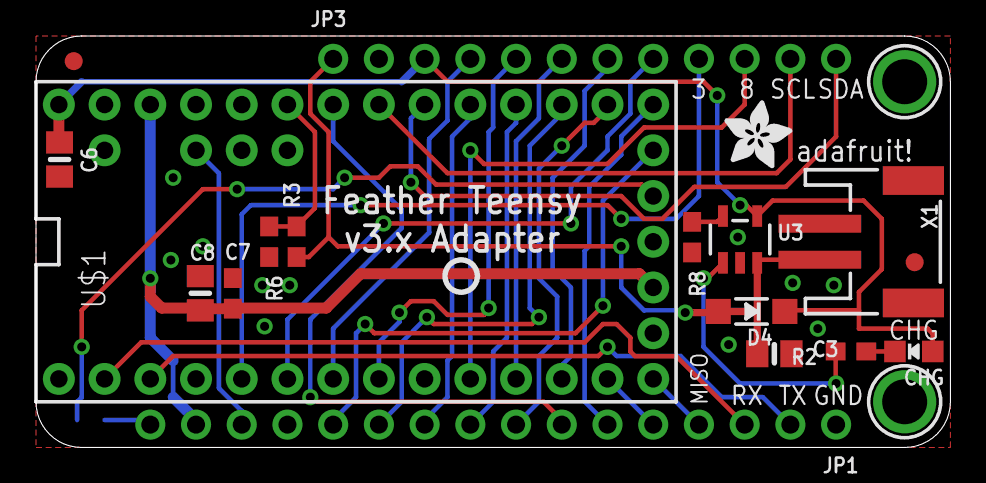
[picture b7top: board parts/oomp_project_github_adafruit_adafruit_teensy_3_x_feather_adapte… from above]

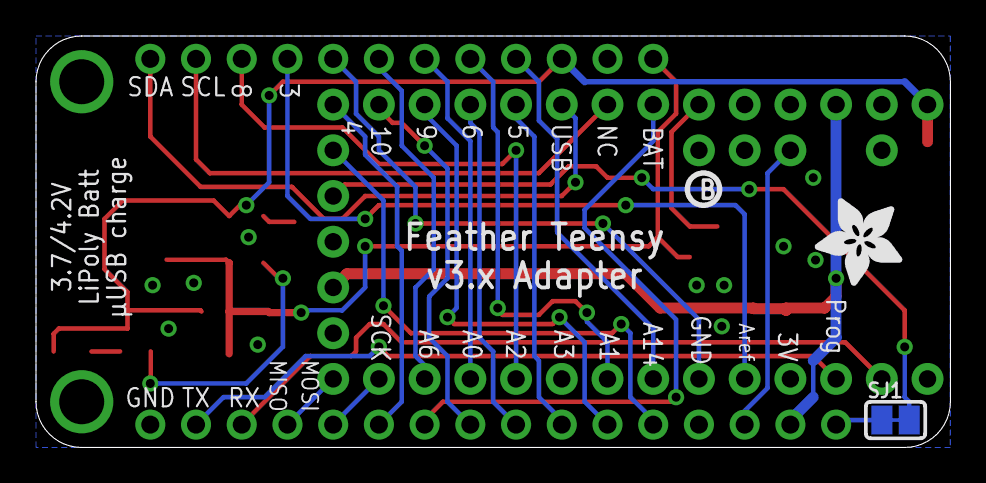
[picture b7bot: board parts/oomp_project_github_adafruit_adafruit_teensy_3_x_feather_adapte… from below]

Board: 2 copper layers, 50.8 x 22.9 mm, 24 parts (3 on the bottom side), 31 nets.

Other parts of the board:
U$4: ADAFRUIT_5MM
U$5, U$6: PCBFEAT-REV-040
U$7: ADAFRUIT_3.5MM

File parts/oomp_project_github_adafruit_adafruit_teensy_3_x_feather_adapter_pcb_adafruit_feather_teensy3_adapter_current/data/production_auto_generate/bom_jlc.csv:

Comment,Designator,Footprint,LCSC Part #
,JP3,Adafruit Feather Teensy3 Adapter-import-fps:1X12_ROUND,C7501588
,JP1,Adafruit Feather Teensy3 Adapter-import-fps:1X16_ROUND,C7501270
,U$7,Adafruit Feather Teensy3 Adapter-import-fps:ADAFRUIT_3.5MM,
,U$4,Adafruit Feather Teensy3 Adapter-import-fps:ADAFRUIT_5MM,
,"U$5,U$6",Adafruit Feather Teensy3 Adapter-import-fps:PCBFEAT-REV-040,
100k,R3,Adafruit Feather Teensy3 Adapter-import-fps:0603-NO,C25803
100K,R6,Adafruit Feather Teensy3 Adapter-import-fps:0603-NO,C25803
10µF,"C3,C6,C8",Adafruit Feather Teensy3 Adapter-import-fps:0805-NO,
1K,R2,Adafruit Feather Teensy3 Adapter-import-fps:0603-NO,C2907002
1uF,C7,Adafruit Feather Teensy3 Adapter-import-fps:0603-NO,C5673
2.2K,R8,Adafruit Feather Teensy3 Adapter-import-fps:0603-NO,C4190
"FIDUCIAL""""","U$34,U$35",Adafruit Feather Teensy3 Adapter-import-fps:FIDUCIAL_1MM,
JSTPH,X1,Adafruit Feather Teensy3 Adapter-import-fps:JSTPH2,
MBR120,D4,Adafruit Feather Teensy3 Adapter-import-fps:SOD-123,
MCP73831T-2ACI/OT,U3,Adafruit Feather Teensy3 Adapter-import-fps:SOT23-5,
ORANGE,CHG0,Adafruit Feather Teensy3 Adapter-import-fps:CHIPLED_0805_NOOUTLINE,
TEENSY_3.1_ALL_PINS,U$1,Adafruit Feather Teensy3 Adapter-import-fps:TEENSY3-ALL_PINS,

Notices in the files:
parts and their libraries:
microbuilder: This work is placed in the public domain, and may be freely used for commercial and non-commercial work with the following conditions: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
